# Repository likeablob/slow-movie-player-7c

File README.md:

<p align="center">
  
  <p align="center">
  <small>From "Spirited Away (2001)" © 2001 Studio Ghibli・NDDTM.</small>
  </p>
</p>

https://user-images.githubusercontent.com/46628917/185350349-dca5a5df-3bee-4c23-829b-23d41562c1f2.mp4

# slow-movie-player-7c

Yet another "Slow Movie Player" implementation with 7-color E-Paper module and ESP32.

Features:

- 7-color E-Paper
- microSD (MMC_SD) as the main storage
- Power management by the ESP32 ULP coprocessor
- Battery operated (12 uA @ Deep Sleep. Runs 1.2 years on a 2000 mAh battery.)

## Table of Contents

- [Background](#background)
- [Install](#install)
- [Usage](#usage)
- [Maintainers](#maintainers)
- [Contributing](#contributing)
- [License](#license)

## Background

A few years later from my previous EPD project [SHIHEN](https://github.com/likeablob/shihen), while being impressed on "Slow Movie" and forks ([[1]](https://hackaday.io/project/179122-slow-ish-movie-player), [[2]](https://github.com/TomWhitwell/SlowMovie)), I was wondering it would be fun if I could also have something bigger and more eye-catching than SHIHEN. One day I found a multi-color E-Paper module available and immediately made an impulse buy. At that time, in [Endless Endless Eight](https://github.com/likeablob/endless-endless-eight/) I had just started learning how powerful ESP32 ULP co-processor is, especially for battery-powered devices. So I decided to make a yet another variant of slow movie player by combining the two components.

The 7-color EPD module has notoriously long refresh time (>= 30 sec), however by delegating BUSY signal handlings to the ULP co-processor, the ESP32 module itself can be stay in Deep Sleep at most of the time.

Given the ESP32 module in the Deep Sleep mode only draws a dozen uA (Actually `12 uA` measured = `6 uA for the module` + `6 uA for peripherals`.), [theoretically the device can survive over a year](https://blc.vercel.app/?config=eyJiYXR0ZXJ5Q2FwYWNpdHkiOiIyMDAwIiwic2xlZXBDdXJyZW50TWlsaXMiOjAuMDEyLCJ3YWtlQ3VycmVudE1pbGlzIjoiMzAiLCJ3YWtldXBDb3VudCI6IjEyIiwid2FrZXVwVW5pdCI6ODY0MDAsIndha2V1cFNlYyI6IjMwIn0) under a 2000 mAh rated battery and 2 hours of wake interval.

## Install

### BOM

_WIP_

- ESP32 (ESP-WROOM-32)
- Waveshare ACeP 7-Color E-Paper Display Module (600x448 5.65inch)
- SMD microSD slot
- microSD card
- M2\*5 screws \* 4
- AAA batteries \* 3

### Wire components

See [./kicad](./kicad).

### Print spacers

See [./openscad](./openscad).

### Build firmware

```sh
$ pio run || pio run # The very 1st run may fail due to ulptool-pio
$ pio run -t upload
```

## Usage

### Prepare video file

Your video file must get converted to a special format before being placed on the microSD.
Simply put `1. Dump video frames to a bunch of PNG images.` `2. Apply palette to the images.` `3. Concat the images into a single file.`

You have several options as follows. After obtaining `index.bin` and `images.bin`, place them onto the root of your FAT32-formatted microSD.

#### Option A: With Docker

```sh
$ cd converter
$ cp path/to/your_vid_file .
$ docker-compose run --rm converter your_vid_file
```

#### Option B: With .sh

- Note that you have to install ffmpeg, ImageMagick, node(v16) beforehand.

```sh
$ cd converter
$ ./convert.sh path/to/your_vid_file
```

#### Option C: By your hand

1. Dump video frames into .png files.

```sh
$ cd converter
$ mkdir -p vid

# -r 1/2 == 0.5 FPS
$ ffmpeg -i path/to/your_vid_file -r 1/2 -vf scale=-1:448,crop=600:448 vid/vid_%06d.png
```

As you may have noticed, you can use any kind of image sources here not only usual video files.

2. Reduce colors with the following 7-color palette.  

```sh
$ mogrify -monitor -dither FloydSteinberg -remap epaper_7c_palette.png vid/*
```

3. Generate `index.bin` and `images.bin`.

```sh
$ npm ci
$ node generate-index-bin.js vid/
```

### How it works

_WIP_

## Maintainers

[@likeablob](https://github.com/likeablob)

## Contributing

PRs accepted.

Small note: If editing the README, please conform to the [standard-readme](https://github.com/RichardLitt/standard-readme) specification.

## License

MIT

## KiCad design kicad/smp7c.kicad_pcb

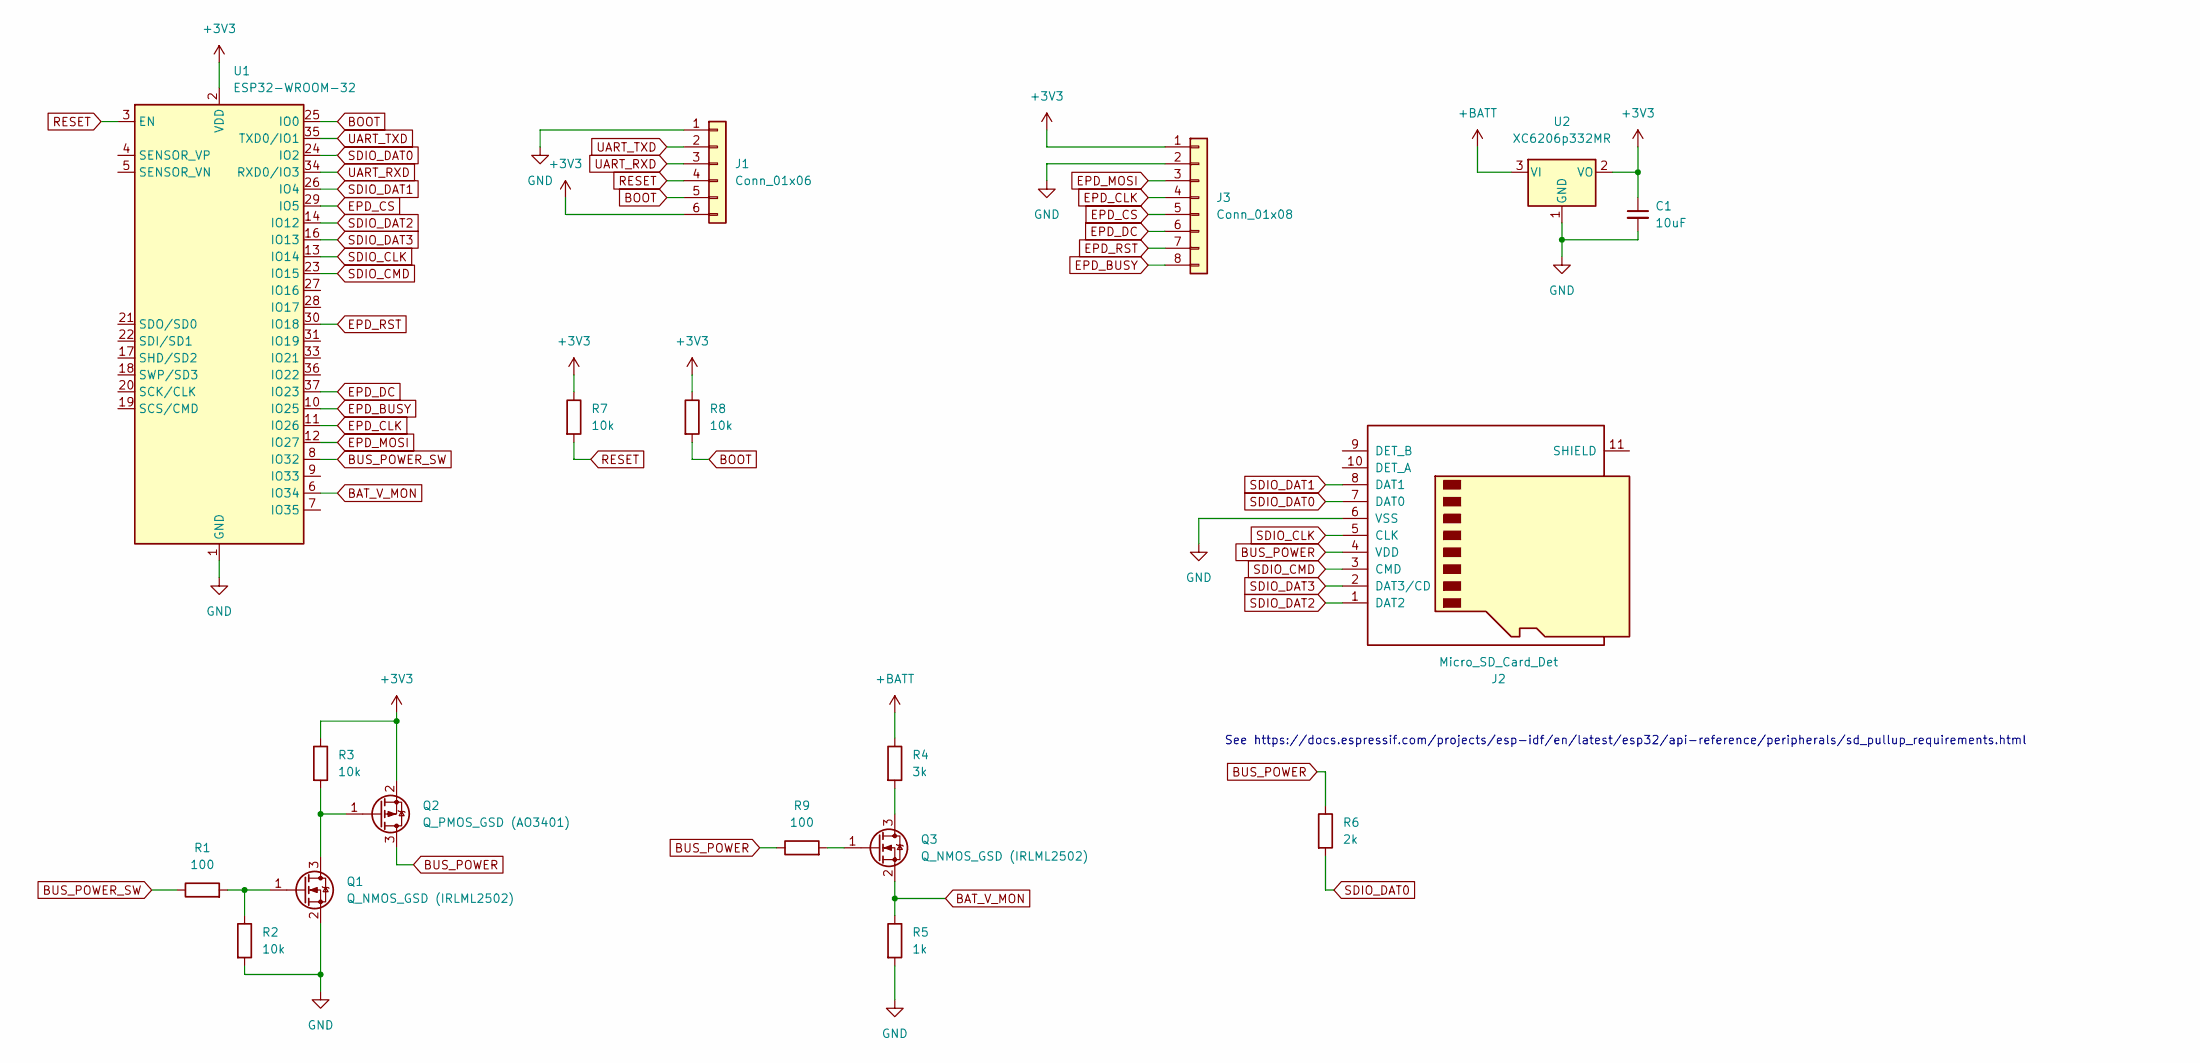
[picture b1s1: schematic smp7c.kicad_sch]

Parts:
C1: 10uF; C_1206_3216Metric
J1: Conn_01x06; PinSocket_1x06_P2.54mm_Vertical
J2: Micro_SD_Card_Det; microSD_HC_Hirose_DM3BT-DSF-PEJS
J3: Conn_01x08; PinSocket_1x08_P2.54mm_Vertical
Q1, Q3: Q_NMOS_GSD (IRLML2502); SOT-23
Q2: Q_PMOS_GSD (AO3401); SOT-23
R1, R9: 100; R_0603_1608Metric
R2, R3, R7, R8: 10k; R_0603_1608Metric
R4: 3k; R_0603_1608Metric
R5: 1k; R_0603_1608Metric
R6: 2k; R_0603_1608Metric
U1: ESP32-WROOM-32
U2: XC6206p332MR; SOT-23

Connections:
+3V3: C1.1, J1.6, J3.1, Q2.2 (S), R3.1, R7.1, R8.1, U1.2 (VDD), U2.2 (VO)
+BATT: R4.1, U2.3 (VI)
BAT_V_MON: Q3.2 (S), R5.1, U1.6 (IO34)
BOOT: J1.5, R8.2, U1.25 (IO0)
BUS_POWER: J2.4 (VDD), Q2.3 (D), R6.1, R9.1
BUS_POWER_SW: R1.1, U1.8 (IO32)
EPD_BUSY: J3.8, U1.10 (IO25)
EPD_CLK: J3.4, U1.11 (IO26)
EPD_CS: J3.5, U1.29 (IO5)
EPD_DC: J3.6, U1.37 (IO23)
EPD_MOSI: J3.3, U1.12 (IO27)
EPD_RST: J3.7, U1.30 (IO18)
GND: C1.2, J1.1, J2.6 (VSS), J3.2, Q1.2 (S), R2.2, R5.2, U1.1 (GND), U1.15 (GND), U1.38 (GND), U1.39 (GND), U2.1 (GND)
unnamed: Q1.1 (G), R1.2, R2.1
unnamed: Q1.3 (D), Q2.1 (G), R3.2
unnamed: Q3.1 (G), R9.2
unnamed: Q3.3 (D), R4.2
RESET: J1.4, R7.2, U1.3 (EN)
SDIO_CLK: J2.5 (CLK), U1.13 (IO14)
SDIO_CMD: J2.3 (CMD), U1.23 (IO15)
SDIO_DAT0: J2.7 (DAT0), R6.2, U1.24 (IO2)
SDIO_DAT1: J2.8 (DAT1), U1.26 (IO4)
SDIO_DAT2: J2.1 (DAT2), U1.14 (IO12)
SDIO_DAT3: J2.2 (DAT3/CD), U1.16 (IO13)
UART_RXD: J1.3, U1.34 (RXD0/IO3)
UART_TXD: J1.2, U1.35 (TXD0/IO1)

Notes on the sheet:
See https://docs.espressif.com/projects/esp-idf/en/latest/esp32/api-reference/peripherals/sd_pullup_requirements.html

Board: 2 copper layers, 18 parts (1 on the bottom side), 26 nets, no tracks yet.

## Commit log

2022-03-19 Add files
2022-03-20 Apply macro constant
2022-03-20 Implement 'random' mode and its build flag
2022-03-24 Remove unused definition
2022-03-24 Replace magic value with macro constant
2022-08-18 Add battery_spacer for fixing batteries properly
    - Rebuild stls
2022-08-18 Implement battery voltage monitoring feature
    - Update schematic to have voltage divider for monitoring
    - Update firmware to monitor voltage and show low voltage notification
